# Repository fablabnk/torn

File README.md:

This is the 42 Berlin fork of the original torn v3 project. We would like to make this project available to anyone in the school who has interest, but first we want to reliably be able to build the project and document any extra steps here.

# Project Status

- Both sides of the keyboard work and can be configured using QMKVia
- Waiting on new PCBs (USB Mini)
- QMKVia flashed (instead of previously just QMK default without Via)

# Next Steps

## Assemble one of the new just Urs and I
- 28th July
- document any remaining issues

## Open project for more people to get involved (at Teatime event Aug 13th)
	- leave the prototype keyboard in cafe and showcase at teatime event on 13th August
	- people can register to the projet via google form
	- order parts and PCBs based on number of registrations
	- set build day (or two days)

## Hosting 'workshop' where we build three or four more

one big day - or a couple of 3 or 4 hour events
deadline

0. Introduction to custom keyboards
- do we have a keyboard 'nerd' we could reach out to and include in the group?
1. Soldering
- solder everything or focus on microcontroller/display first
2. Flashing QMK/Via
- keep dedicated flashing setup on hand
- note that this was done by the previous group so we need to figure out how it works and documents
3. Configuration
- 
4. Case

# To Do

- Get LEDs working - LEDs are apparently not configured in the current QMK firmware
	- Define the correct pin assignments for the LEDs in config.h.
	- Implement the appropriate LED control functions in your keymap or keyboard .c file, such as led_set_user() for lock indicators or custom code for other uses.

- Solve display glitching issue
	- probably hardware related as we tested with another half which doesn't glitch

- add this line to build-guide.md
	- In order to call 'make' the qmk cli has to be installed. Follow the instructions [here](https://docs.qmk.fm/newbs_getting_started).

- Make one default layout that everyone gets at the beginning

# Documented Issues

## Flashing the Bootloader

We have an Arduino set aside in a box to help with flashing the bootloader
The original guide has the right instructions in terms of pinouts, but it's easy to the wiring up, so for 2nd build we should to document better how to wire the pins to the 6-pin header on the keyboard (photo)

## Flashing the Firmware

There were two issues here that diverged from the build guide. We installed all the necessary dependencies and tools in the LabAdmin account on the computer on the left next to the window.

- QMKVia which torn v3 uses is no longer supported. We don't have a solution for this, as the support for it its dropped and requires manual intervention and investigation as mentioned in the author isse https://github.com/rtitmuss/torn/issues/29

- The make command to be run from the qmk_firmware folder is ```make torn:default:flash``` as opposed to the guide. Keyboard must be set to flashing mode.

## Layout Configuration

- A C file is used to configure the keyboard [keymap file](https://github.com/qmk/qmk_firmware/blob/master/keyboards/torn/keymaps/default/keymap.c). This could be improved by adding a wrapper. Any alterations require compiling and flashing to the chip, which could complicate things though

## Button Height

The choice of height of the two reset/boot buttons is important. For the first build we used very flat buttons, only later to discover that they are inaccessible when adding the transparent acrylic layer on top. The solution to this would be to use taller buttons (we have them in different sizes in a kit) and to cut holes in the acrylic layer to allow the buttons to poke through.

## Choice of Case

It helps to consider which case you might build even from the get-go, as it can affect which buttons you choose (see below) and for some cases the switches/keycaps need to be of a certain type.

What we tried to far:
- PCB Case: We noted that there are no .svg files provided for laser cutting the parts, we must create our own from the Kicad projects (base and plate). This requires a few design decisions (indent around USB connector etc)
- HiPro Case: Be aware that there are two variations here for MX or Choc switches

# FAQ

## What is VIA and how does it work?

VIA is a software tool that allows you to dynamically remap keys and configure your keyboard layout in real time—without needing to reflash the firmware each time you want to make a change. Carlo and co didn't get this to work and filed this issue: https://github.com/rtitmuss/torn/issues/29

- Keys are organised in categories - can be character or functions
- Layers at Tip Left
- Keys show both click and hold functions
- If Via doesn't provide the functionality you need, you can alway use QMK syntax by using the "Any" wildcard key, which lets you hardcode QMK keycode e.g. LT(2, KC_DEL) which when holding delete will put you in layer 2
- Here is a basic (cheat sheet)[https://docs.qmk.fm/keycodes_basic] for QMK keycodes

One issue we had is how to flash QMKVia, as:
- VIA keymaps are no longer held in the main QMK git repository.
- You will need to either compile a default one, write your own one, or follow the instructions to add the VIA userspace repository.
- See https://docs.qmk.fm/ChangeLog/20240526#migration-of-via-keymaps-to-via-team-control

## What firmware is running on the keyboard now?

QMK default

## How to flash QMK again in order to update the keyboard configuration?

See QMK section of torn build guide: https://github.com/rtitmuss/torn/blob/master/doc/build.md

## What are LEDs for and how to configure them?

Caps Lock, Num Lock, and Scroll Lock

## Are button row of keys even working?

In keymap.c, we can see the real function of these keys in the QWERTY layer
Left:	R_DEL,   KC_LCTL, S_BSPC,  R_DEL
Right:	G_ENT,   L_SPC,   KC_RALT, G_ENT

Note: don't trust keymap.c ASCII, configuration differs (so UP arrow being above DOWN)

Layers do work e.g.
- On left side of keyboard, 1st and 4th key R_DEL
	- performs delete when tapped
	- moves to RAISE layer when held
- On the right side of the keyboard, 2nd key L_SPC 
	- perform space when tapped
	- goes into lower mode when held 

Note: KC_TRNS or _______ means to look down to the next layer for the underlying function of the key

## What are rotary encoders typically used for?

- Scrolling (vertical or horizontal in documents/web pages)
- Undo/redo
- Zoom in/out
- Tab or window switching
- Launching macros or custom shortcuts.

# Remapping

This means editing the QMK keymap.c file within the QMK firmware and reflashing the firmware
https://github.com/qmk/qmk_firmware/blob/master/keyboards/torn/keymaps/default/keymap.c
- we don't want to do this right now!

https://github.com/qmk/qmk_firmware/tree/master/keyboards/torn

// https://github.com/rtitmuss/torn/issues/29

# Via Setup

# Setup your torn keyboard with via

## QMK Setup
 - Set up QMK Firmware including CLI like described [here](https://docs.qmk.fm/newbs_getting_started)
 - In order to get it running on linux I actually had to update my PATH varaiable accordingly (see  'Note on Debian, Ubuntu and their derivatives')

## get External QMK Userspace 
 - Instead of cloning the QMK-Firmware from the github, get the [QMK userspace via](https://github.com/the-via/qmk_userspace_via) repo and use it with the CLI instead.
 - I think one could also get the original firmware and change all the configs accordingly, however this one is already onfigured to work with VIA.

## Flash Torn 
 - Now inside the root folder, use the CLI to either compile:
 `qmk compile -kb torn -km via`
 or directly flash the updated keyboard firmware:
 `qmk flash -kb torn -km via`
 -> in order to flash, i usually have to reconnect the keyboard, wait until the oled shows 'TORN' and go into boot mode: like described [here](https://github.com/fablabnk/torn/blob/master/doc/build.md) in chapter QMK

## Configure using VIA 
 - After successfully flashing, I dis and reconnect the keyboard again and open the [via app](https://www.usevia.app/) in a chromium based browser or the Desktop app, which is available for download [here](https://github.com/the-via/releases/releases/)

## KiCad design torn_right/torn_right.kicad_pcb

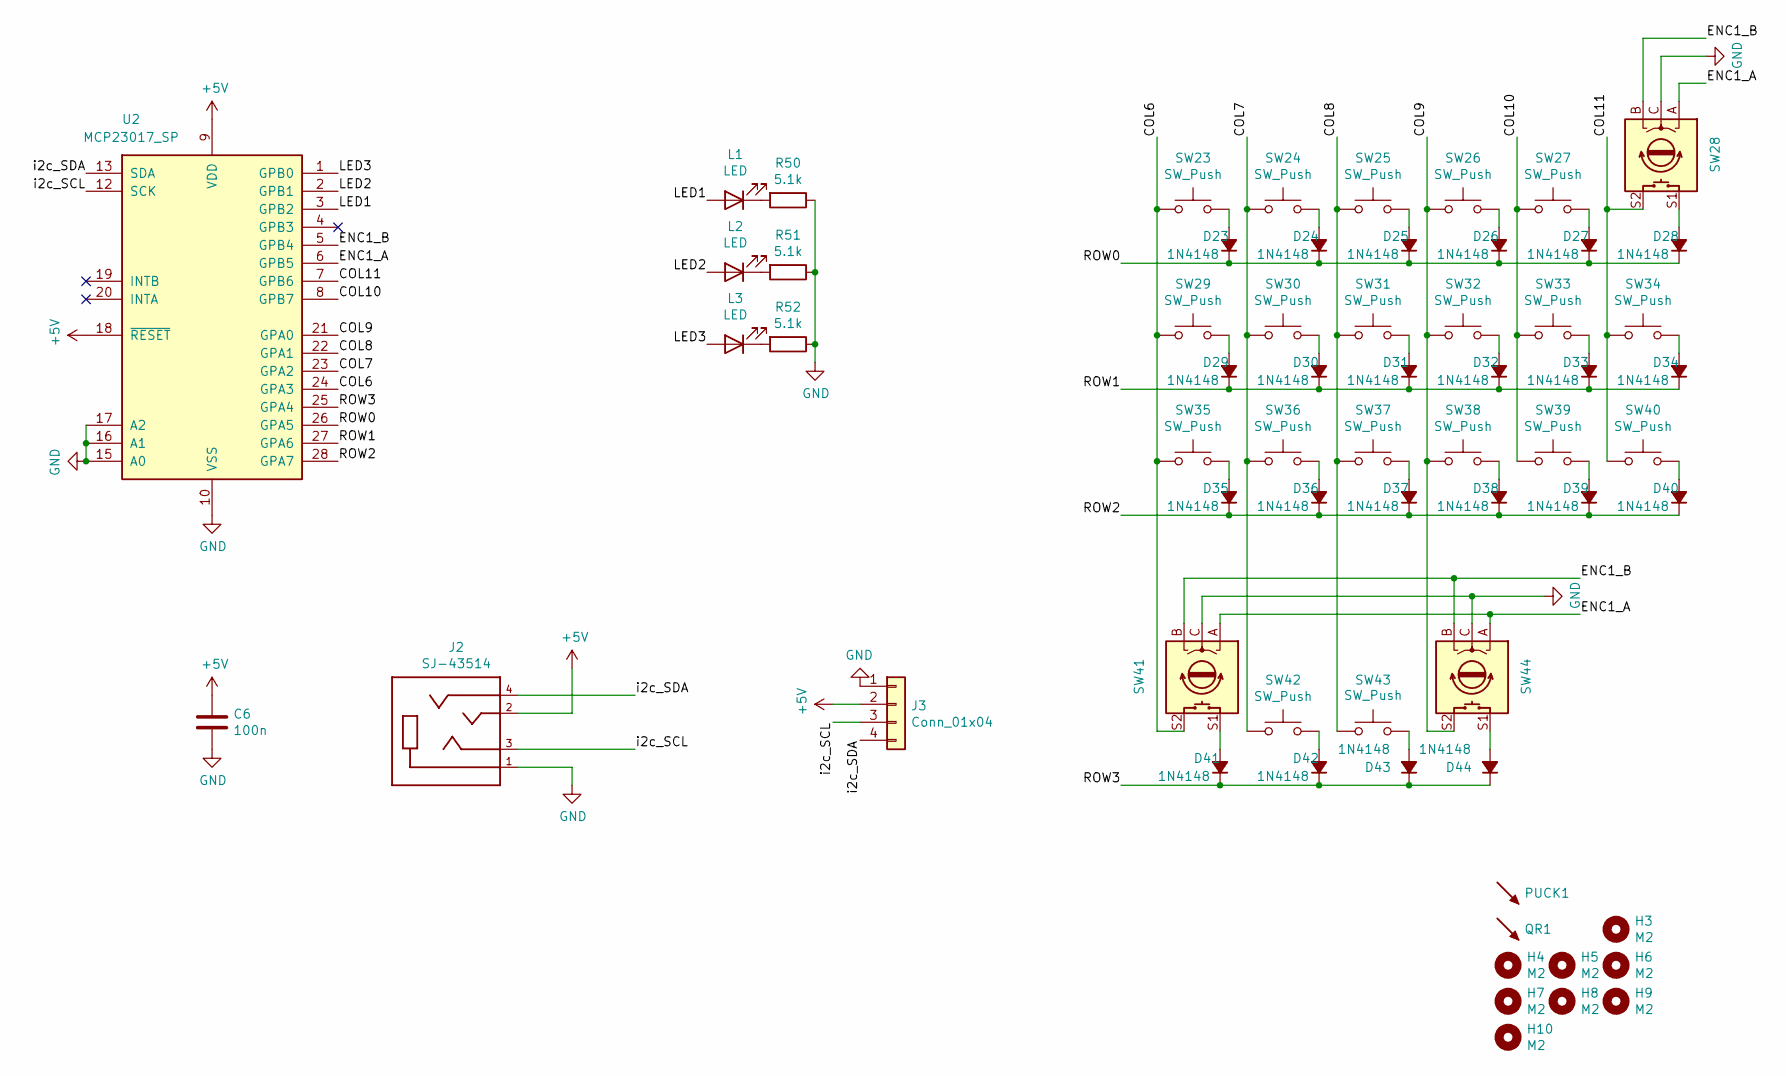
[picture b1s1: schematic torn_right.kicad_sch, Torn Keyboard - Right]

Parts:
C6: 100n; C_Disc_D4.3mm_W1.9mm_P5.00mm
D23, D24, D25, D26, D27, D28, D29, D30, D31, D32, D33, D34, D35, D36, D37, D38, D39, D40, D41, D42, D43, D44: 1N4148; D_DO-35_SOD27_P5.08mm_Horizontal
H3, H4, H5, H6, H7, H8, H9, H10: M2; MountingHole_2.2mm_M2_Pad
J2: SJ-43514; PJ-320A
J3: Conn_01x04; OLED_1side
L1, L2, L3: LED; LED_D3.0mm
PUCK1: PUCK; Tenting_Puck
QR1: SYM_Arrow45_Small; torn_qr_code
R50, R51, R52: 5.1k; R_Axial_DIN0207_L6.3mm_D2.5mm_P7.62mm_Horizontal
SW23, SW24, SW25, SW26, SW27, SW29, SW30, SW31, SW32, SW33, SW34, SW35, SW36, SW37, SW38, SW39, SW40, SW42, SW43: SW_Push; Kailh_socket_MX_PG1350_optional
SW28, SW41, SW44: Rotary_Encoder_Switch; Kailh_socket_MX_PG1350_EC11_optional
U2: MCP23017_SP; DIP-28_W7.62mm_Socket

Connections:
+5V: C6.1, J2.2, J3.2, U2.9 (VDD), U2.18 (~RESET)
/COL6: SW23.2, SW29.2, SW35.2, SW41.S2, U2.24 (GPA3)
/COL7: SW24.2, SW30.2, SW36.2, SW42.2, U2.23 (GPA2)
/COL8: SW25.2, SW31.2, SW37.2, SW43.2, U2.22 (GPA1)
/COL9: SW26.2, SW32.2, SW38.2, SW44.S2, U2.21 (GPA0)
/COL10: SW27.2, SW33.2, SW39.2, U2.8 (GPB7)
/COL11: SW28.S2, SW34.2, SW40.2, U2.7 (GPB6)
/ENC1_A: SW28.A, SW41.A, SW44.A, U2.6 (GPB5)
/ENC1_B: SW28.B, SW41.B, SW44.B, U2.5 (GPB4)
/LED1: L1.2 (A), U2.3 (GPB2)
/LED2: L2.2 (A), U2.2 (GPB1)
/LED3: L3.2 (A), U2.1 (GPB0)
/ROW0: D23.1 (K), D24.1 (K), D25.1 (K), D26.1 (K), D27.1 (K), D28.1 (K), U2.26 (GPA5)
/ROW1: D29.1 (K), D30.1 (K), D31.1 (K), D32.1 (K), D33.1 (K), D34.1 (K), U2.27 (GPA6)
/ROW2: D35.1 (K), D36.1 (K), D37.1 (K), D38.1 (K), D39.1 (K), D40.1 (K), U2.28 (GPA7)
/ROW3: D41.1 (K), D42.1 (K), D43.1 (K), D44.1 (K), U2.25 (GPA4)
/i2c_SCL: J2.3, J3.3, U2.12 (SCK)
/i2c_SDA: J2.4, J3.4, U2.13 (SDA)
GND: C6.2, J2.1, J3.1, R50.1, R51.1, R52.1, SW28.C, SW41.C, SW44.C, U2.10 (VSS), U2.15 (A0), U2.16 (A1), U2.17 (A2)
unnamed: D23.2 (A), SW23.1
unnamed: D24.2 (A), SW24.1
unnamed: D25.2 (A), SW25.1
unnamed: D26.2 (A), SW26.1
unnamed: D27.2 (A), SW27.1
unnamed: D28.2 (A), SW28.S1
unnamed: D29.2 (A), SW29.1
unnamed: D30.2 (A), SW30.1
unnamed: D31.2 (A), SW31.1
unnamed: D32.2 (A), SW32.1
unnamed: D33.2 (A), SW33.1
unnamed: D34.2 (A), SW34.1
unnamed: D35.2 (A), SW35.1
unnamed: D36.2 (A), SW36.1
unnamed: D37.2 (A), SW37.1
unnamed: D38.2 (A), SW38.1
unnamed: D39.2 (A), SW39.1
unnamed: D40.2 (A), SW40.1
unnamed: D41.2 (A), SW41.S1
unnamed: D42.2 (A), SW42.1
unnamed: D43.2 (A), SW43.1
unnamed: D44.2 (A), SW44.S1
unnamed: L1.1 (K), R50.2
unnamed: L2.1 (K), R51.2
unnamed: L3.1 (K), R52.2

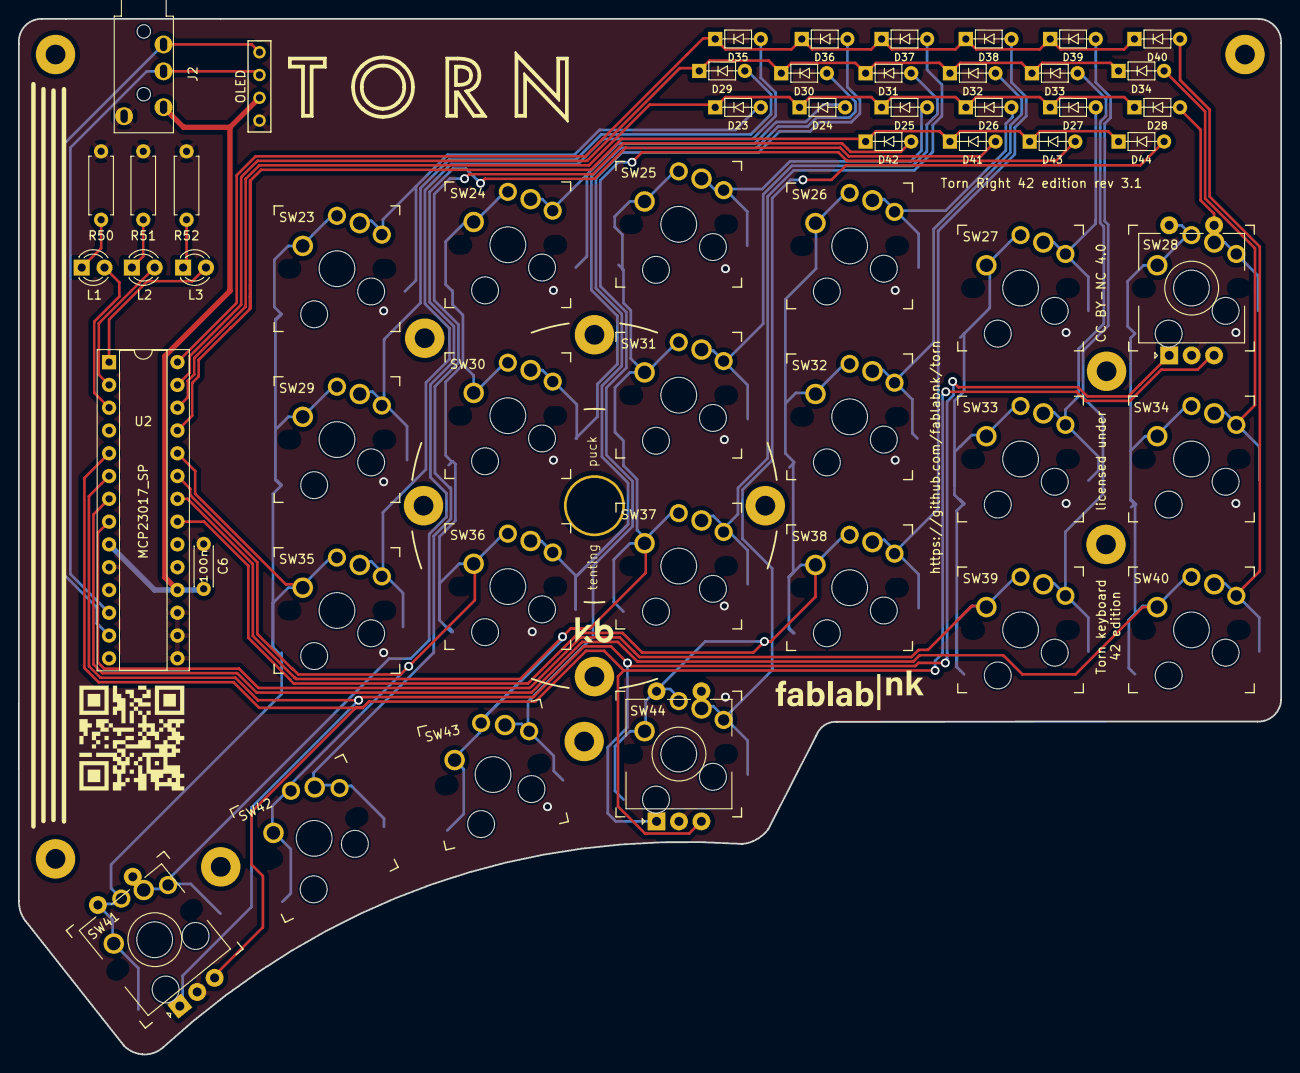
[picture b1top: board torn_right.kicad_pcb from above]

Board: 2 copper layers, 140.7 x 115.4 mm, 64 parts (0 on the bottom side), 44 nets.

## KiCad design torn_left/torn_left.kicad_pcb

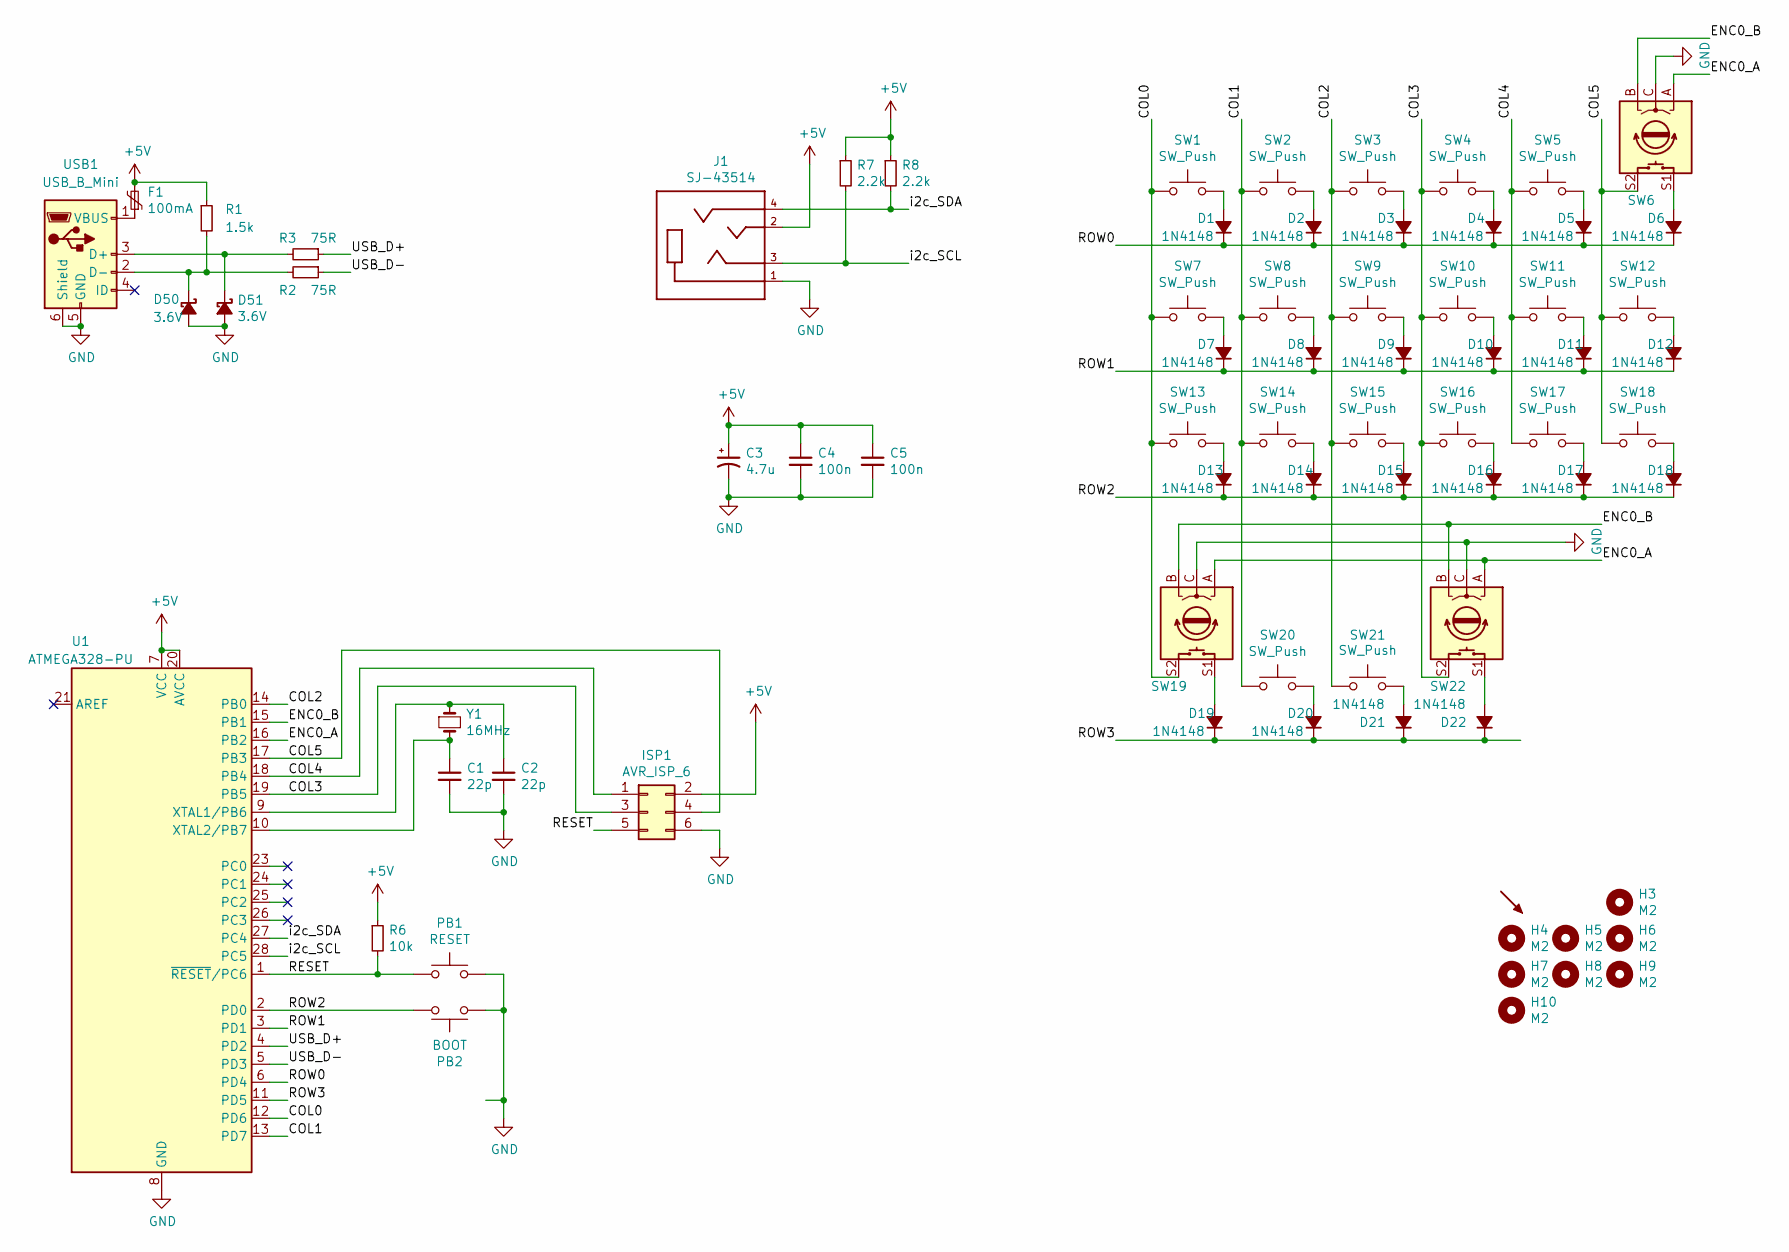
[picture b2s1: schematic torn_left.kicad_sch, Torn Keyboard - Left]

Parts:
C1, C2: 22p; C_Disc_D3.0mm_W1.6mm_P2.50mm
C3: 4.7u; CP_Radial_D4.0mm_P1.50mm
C4, C5: 100n; C_Disc_D4.3mm_W1.9mm_P5.00mm
D1, D2, D3, D4, D5, D6, D7, D8, D9, D10, D11, D12, D13, D14, D15, D16, D17, D18, D19, D20, D21, D22: 1N4148; D_DO-35_SOD27_P5.08mm_Horizontal
D50, D51: 3.6V; D_DO-35_SOD27_P5.08mm_Horizontal
F1: 100mA; polyfuse_5.1mm
H3, H4, H5, H6, H7, H8, H9, H10: M2; MountingHole_2.2mm_M2_Pad
ISP1: AVR_ISP_6; AVR_ICSP_3x2
J1: SJ-43514; PJ-320A
PB1: RESET; SW_PUSH_6mm
PB2: BOOT; SW_PUSH_6mm
PUCK1: SYM_Arrow45_Small; Tenting_Puck
R1: 1.5k; R_Axial_DIN0207_L6.3mm_D2.5mm_P7.62mm_Horizontal
R2, R3: 75R; R_Axial_DIN0207_L6.3mm_D2.5mm_P7.62mm_Horizontal
R6: 10k; R_Axial_DIN0207_L6.3mm_D2.5mm_P7.62mm_Horizontal
R7, R8: 2.2k; R_Axial_DIN0207_L6.3mm_D2.5mm_P7.62mm_Horizontal
SW1, SW2, SW3, SW4, SW5, SW7, SW8, SW9, SW10, SW11, SW12, SW13, SW14, SW15, SW16, SW17, SW18, SW20, SW21: SW_Push; Kailh_socket_MX_PG1350_optional
SW6, SW19, SW22: Rotary_Encoder_Switch; Kailh_socket_MX_PG1350_EC11_optional
U1: ATMEGA328-PU; DIP-28_W7.62mm_Socket
USB1: USB_B_Mini; USB-B-Mini-Right-Angled
Y1: 16MHz; Crystal_HC49-4H_Vertical

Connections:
+5V: C3.1, C4.1, C5.1, F1.2, ISP1.2, J1.2, R1.1, R6.1, R7.1, R8.1, U1.7 (VCC), U1.20 (AVCC)
/COL0: SW1.2, SW7.2, SW13.2, SW19.S2, U1.12 (PD6)
/COL1: SW2.2, SW8.2, SW14.2, SW20.2, U1.13 (PD7)
/COL2: SW3.2, SW9.2, SW15.2, SW21.2, U1.14 (PB0)
/COL3: ISP1.3, SW4.2, SW10.2, SW16.2, SW22.S2, U1.19 (PB5)
/COL4: ISP1.1, SW5.2, SW11.2, SW17.2, U1.18 (PB4)
/COL5: ISP1.4, SW6.S2, SW12.2, SW18.2, U1.17 (PB3)
/ENC0_A: SW6.A, SW19.A, SW22.A, U1.16 (PB2)
/ENC0_B: SW6.B, SW19.B, SW22.B, U1.15 (PB1)
/RESET: ISP1.5, PB1.1, R6.2, U1.1 (~RESET/PC6)
/ROW0: D1.1 (K), D2.1 (K), D3.1 (K), D4.1 (K), D5.1 (K), D6.1 (K), U1.6 (PD4)
/ROW1: D7.1 (K), D8.1 (K), D9.1 (K), D10.1 (K), D11.1 (K), D12.1 (K), U1.3 (PD1)
/ROW2: D13.1 (K), D14.1 (K), D15.1 (K), D16.1 (K), D17.1 (K), D18.1 (K), PB2.2, U1.2 (PD0)
/ROW3: D19.1 (K), D20.1 (K), D21.1 (K), D22.1 (K), U1.11 (PD5)
/USB_D+: R3.1, U1.4 (PD2)
/USB_D-: R2.1, U1.5 (PD3)
/i2c_SCL: J1.3, R7.2, U1.28 (PC5)
/i2c_SDA: J1.4, R8.2, U1.27 (PC4)
GND: C1.2, C2.2, C3.2, C4.2, C5.2, D50.2 (A), D51.2 (A), ISP1.6, J1.1, PB1.2, PB2.1, SW6.C, SW19.C, SW22.C, U1.8 (GND), U1.22 (GND), USB1.5 (GND), USB1.6 (Shield)
unnamed: D1.2 (A), SW1.1
unnamed: D2.2 (A), SW2.1
unnamed: D3.2 (A), SW3.1
unnamed: D4.2 (A), SW4.1
unnamed: D5.2 (A), SW5.1
unnamed: D6.2 (A), SW6.S1
unnamed: D7.2 (A), SW7.1
unnamed: D8.2 (A), SW8.1
unnamed: D9.2 (A), SW9.1
unnamed: D10.2 (A), SW10.1
unnamed: D11.2 (A), SW11.1
unnamed: D12.2 (A), SW12.1
unnamed: D13.2 (A), SW13.1
unnamed: D14.2 (A), SW14.1
unnamed: D15.2 (A), SW15.1
unnamed: D16.2 (A), SW16.1
unnamed: D17.2 (A), SW17.1
unnamed: D18.2 (A), SW18.1
unnamed: D19.2 (A), SW19.S1
unnamed: D20.2 (A), SW20.1
unnamed: D21.2 (A), SW21.1
unnamed: D22.2 (A), SW22.S1
unnamed: D50.1 (K), R1.2, R2.2, USB1.2 (D-)
unnamed: D51.1 (K), R3.2, USB1.3 (D+)
unnamed: C2.1, U1.9 (XTAL1/PB6), Y1.1
unnamed: C1.1, U1.10 (XTAL2/PB7), Y1.2
unnamed: F1.1, USB1.1 (VBUS)

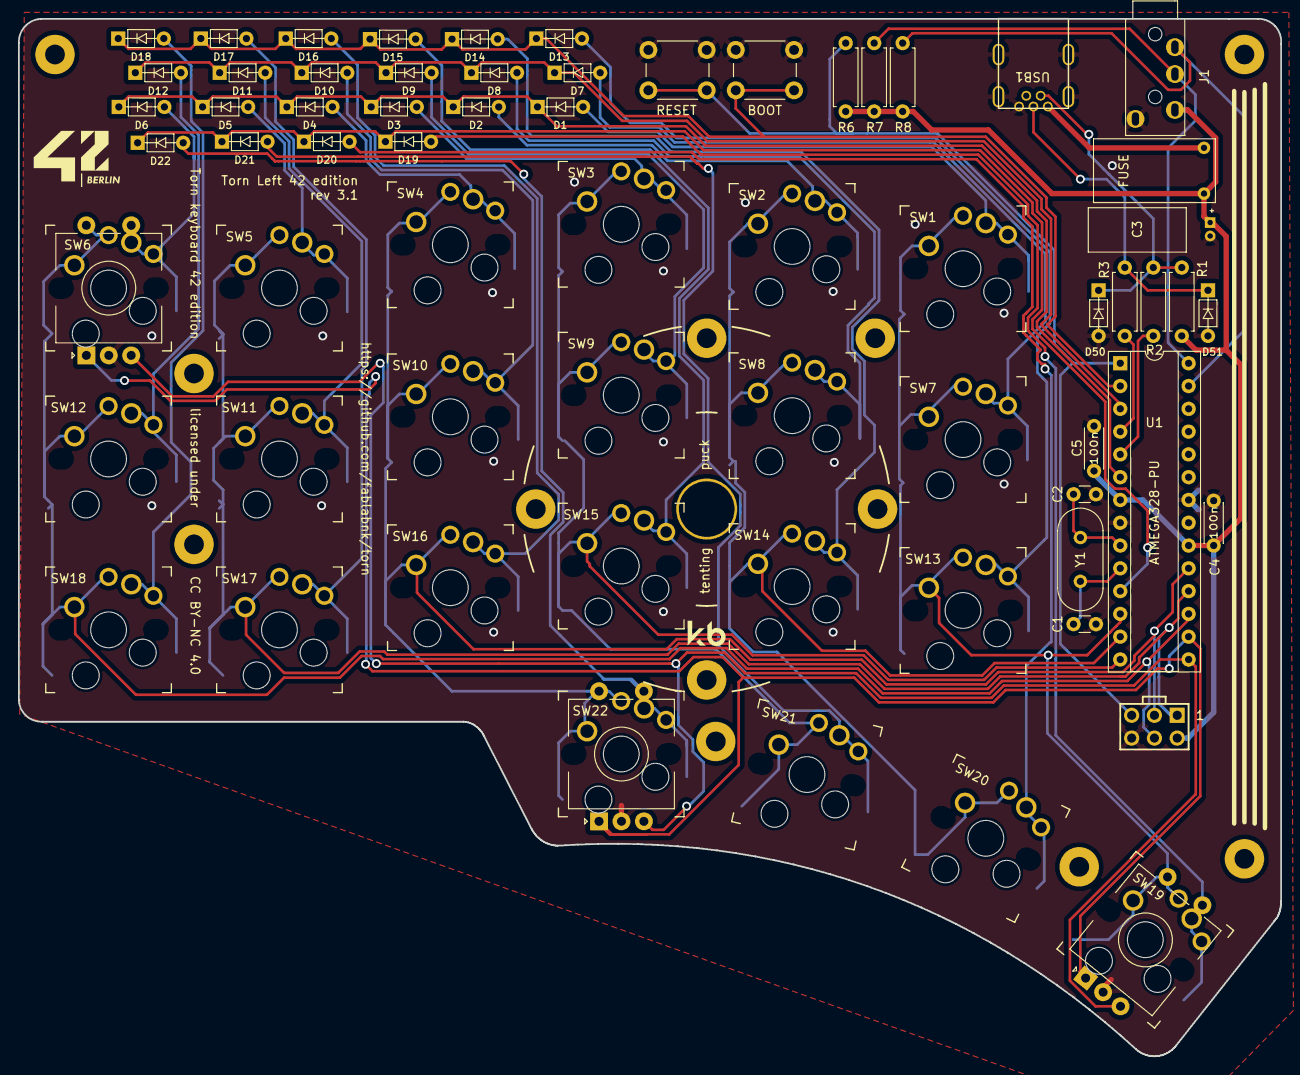
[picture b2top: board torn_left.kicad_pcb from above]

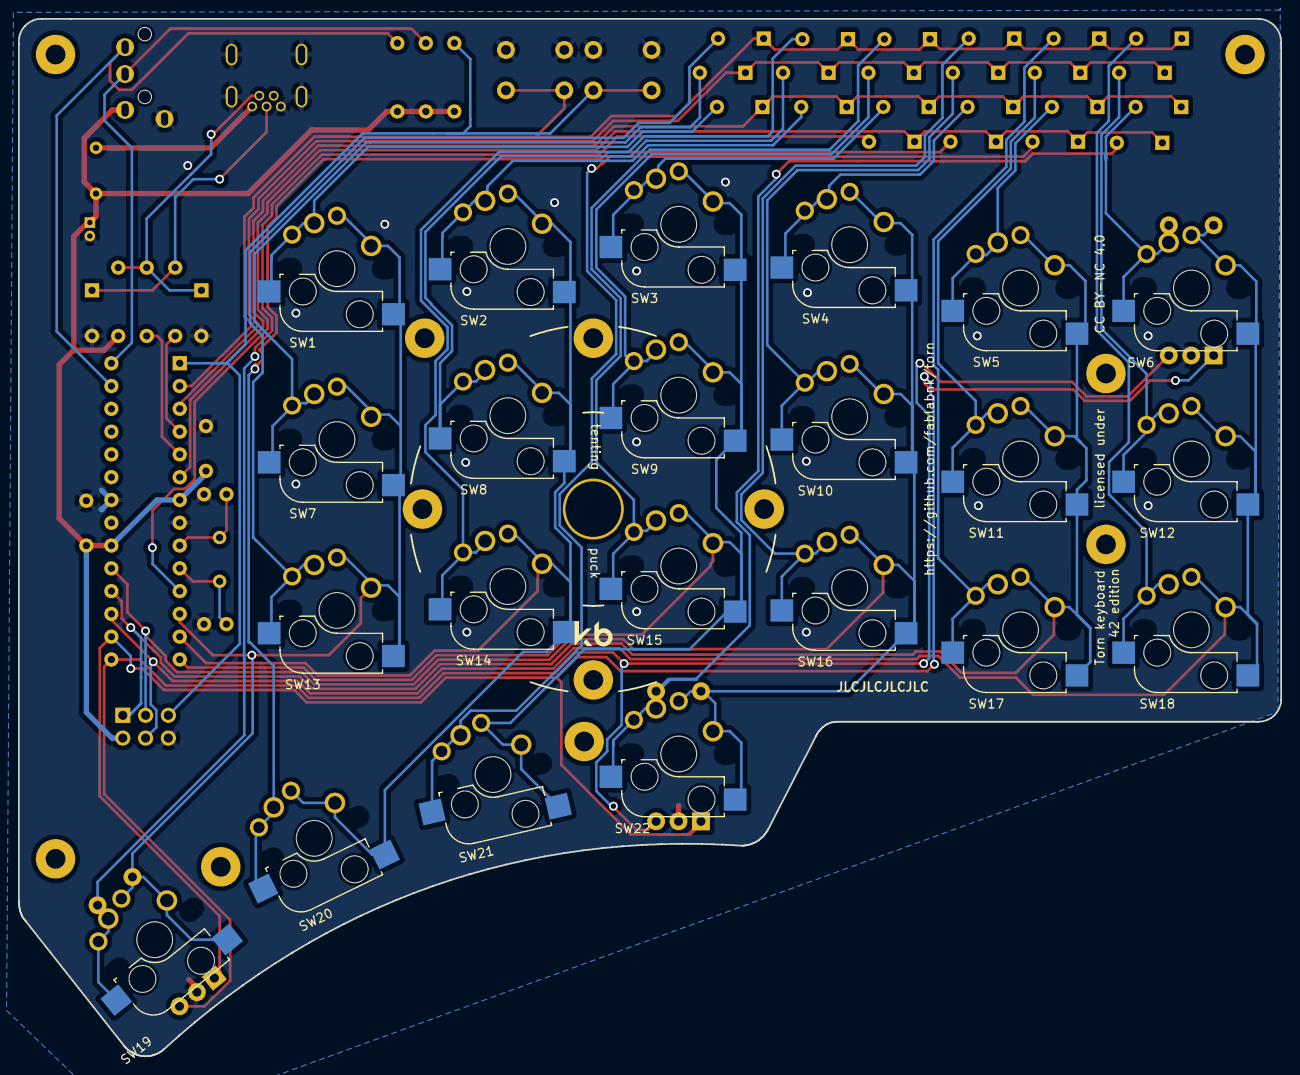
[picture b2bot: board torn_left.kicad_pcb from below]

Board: 2 copper layers, 140.7 x 115.6 mm, 74 parts (8 on the bottom side), 46 nets.

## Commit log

2025-04-24 preparing for new board revision
2025-07-14 committing before changing to standard size through hole resistors
2025-07-14 changed resistor sizes to more common 1/4W 0207DIN sizes on both boards
2025-08-11 added TornFlashGuide.md documented how to flash bootloader using ArduinoISP and then firmware (including via)
2025-11-06 committing before switching out right hand TRRS connector
2025-11-06 right board updated with proper TRRS and other fixes - reminder to check left side passes DRC

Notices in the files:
torn_left/torn_left.kicad_pcb:
Torn keyboard 42 edition licensed under CC BY-NC 4.0
Torn keyboard licensed under CC BY-NC 4.0
